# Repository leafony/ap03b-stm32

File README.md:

# Leafony AP03B STM32

AP03B STM32は、STM32duinoの既存のボード選択「Leafony AP03」を使用するマイコンリーフです。v1.1ではLQFP64の各GPIOを従来と同じLeafonyバス接点に接続します。

STM32L452RET6を搭載した、Leafony AP03B STM32リーフのハードウェア設計リポジトリです。KiCadの回路図・PCBレイアウト、単体基板のGerber・ドリルデータ、専用ライブラリ、部品表（BOM）を収録しています。

設計を開く場合は [KiCadプロジェクト](./kicad/ap03b-stm32/ap03b-stm32.kicad_pro)、部品を確認する場合は [BOM](./docs/leafony-ap03b-stm32-bom.csv) から参照してください。

## ハードウェア概要

| 項目 | 内容 |
| --- | --- |
| MCU | STMicroelectronics STM32L452RET6（U1） |
| CPU | Arm Cortex-M4、FPU搭載、最大80 MHz |
| メモリ | Flash 512 KB / SRAM 160 KB |
| MCUパッケージ | LQFP64、10 × 10 mm、0.5 mmピッチ |
| 低速外部クロック | 32.768 kHz水晶（X1） |
| 電源 | Leafonyバスの3.3 V / GND |
| バス接点 | CN1、表裏各29接点 |
| 主なバス信号 | D0〜D13、A0〜A5、SDA / SCL、SWDIO / SWCLK、RESET、AREF |
| 操作・表示 | BOOT0切り替えスイッチ、リセットスイッチ、BOOT0状態表示LED |
| 基板 | 外形最大23 × 20 mm、4層、板厚0.8 mm（PCB設計値） |
| 製造仕様 | FR-4、無電解金めっき（ENIG）。L2はGND専用層。L1・L3・L4は信号・電源を配線し、空き領域をGNDで充填。表裏のCN1バス接点のマスク開口部はGND充填の対象外 |
| 配線・ビア | 最小配線幅・間隔は0.15 mm。ビアは外径0.45 mm・穴径0.25 mmのパッド外貫通ビア |
| 設計リビジョン | v1.1、2026-11-20（単体基板・回路図のタイトル欄） |

CPU・メモリの仕様は [STMicroelectronicsの製品情報](https://www.st.com/en/microcontrollers-microprocessors/stm32l452re.html)、実装部品と接続は本リポジトリの回路図・PCB・BOMを参照しています。最大クロックはMCUの仕様値で、実際の動作クロックはファームウェアの設定によります。

CN1のVBUS端子は未接続で、AREFの接続用抵抗R5は未実装（DNP）です。各端子の接続は [Leafonyバス回路図](./kicad/ap03b-stm32/leafony_bus.kicad_sch) と [MCU回路図](./kicad/ap03b-stm32/stm32.kicad_sch) で確認できます。

### スイッチとLED

| 部品 | 型番 | 回路上の役割 |
| --- | --- | --- |
| SW1（PG） | CUS-12TB | BOOT0のHigh / Lowを切り替える |
| SW2（RST） | EVQ-P7B01P | 押すとRESETをGNDへ接続する |
| D1 | SML-A12U8TT86 | BOOT0がHighのときに点灯する。発光面は基板下辺の外側を向く |

### D1のリール供給と実装方向

ROHMの品番別仕様書（Rev.009）の図1とT86テーピング図を、次のように対応させます。供給姿勢から基板姿勢への変換は面内の回転だけです。[ROHM SML-A12U8TT86仕様書、4・5・11ページ](https://fscdn.rohm.com/en/products/databook/datasheet/opto/led/chip_mono/sml-a12u8tt86-e.pdf)

| 見る向き | カソード（K） | アノード（A） | 発光窓 |
| --- | --- | --- | --- |
| T86テープを吸着側から見て、送り穴を上に置く | 上・送り穴側 | 下 | 右 |
| 基板を部品面から見て、Leafonyバスを上に置く | 右・パッド1（GND） | 左・パッド2（R6側） | 下・基板外側 |

この二つの図の間では部品を時計回りに90°回転します。KiCadの実装座標ではD1は表面、回転角180°です。こちらの角度はフットプリントの0°を基準にしており、装着機の角度はフィーダーの取付方向と部品ライブラリの0°設定に合わせます。実装座標の原点は2ランドの中心間の中点で、F.Fab層には筐体と発光窓の輪郭を表示します。[D1の実装座標（KiCad、単位mm）](./kicad/ap03b-stm32/fabrication/ap03b-stm32-v1.1-D1-pos.csv)

U1・U2・Q1の1番ピンは、表面シルクの塗りつぶし三角が指す端子です。

詳細は [リセット・プログラム切り替え回路](./kicad/ap03b-stm32/reset_prog.kicad_sch) を参照してください。

## リポジトリ構成

| パス | 内容 |
| --- | --- |
| [kicad/ap03b-stm32/ap03b-stm32.kicad_pro](./kicad/ap03b-stm32/ap03b-stm32.kicad_pro) | 単体基板のKiCadプロジェクト |
| [kicad/ap03b-stm32/ap03b-stm32.kicad_sch](./kicad/ap03b-stm32/ap03b-stm32.kicad_sch) | トップレベル回路図。以下の3シートをまとめる |
| [kicad/ap03b-stm32/stm32.kicad_sch](./kicad/ap03b-stm32/stm32.kicad_sch) | MCU、電源、クロック周辺回路 |
| [kicad/ap03b-stm32/leafony_bus.kicad_sch](./kicad/ap03b-stm32/leafony_bus.kicad_sch) | Leafonyバス接点と信号接続 |
| [kicad/ap03b-stm32/reset_prog.kicad_sch](./kicad/ap03b-stm32/reset_prog.kicad_sch) | リセット、BOOT0切り替え、LED、信号切り替え回路 |
| [kicad/ap03b-stm32/ap03b-stm32.kicad_pcb](./kicad/ap03b-stm32/ap03b-stm32.kicad_pcb) | 単体基板のPCBレイアウト |
| [単体基板のGerber・ドリル（v1.1）](./kicad/ap03b-stm32/fabrication/ap03b-stm32-v1.1.zip) | 4層のGerber、積層情報、めっき穴と非めっき穴のドリル |
| [kicad/ap03b-stm32/panelized/](./kicad/ap03b-stm32/panelized/) | 旧版（UFBGA64・6層）の面付け基板 |
| [kicad/ap03b-stm32/panelized/Gerber/](./kicad/ap03b-stm32/panelized/Gerber/) | 旧版面付け基板のGerber・ドリルデータ |
| [kicad/ap03b-stm32/lib/](./kicad/ap03b-stm32/lib/) | Leafony専用シンボル、フットプリント、3Dモデル配置先 |
| [docs/leafony-ap03b-stm32-bom.csv](./docs/leafony-ap03b-stm32-bom.csv) | 部品表（CSV） |
| [examples/](./examples/) | サンプルコード用ディレクトリ。現時点ではコード未収録 |

KiCadプロジェクト名は `ap03b-stm32` で、設計ファイルは `kicad/ap03b-stm32/` にまとめています。

## KiCadで開く

回路図とPCBは **KiCad 10.0** で保存されています。KiCad 10.0形式を読み込める環境と、KiCad標準のシンボル・フットプリントライブラリを用意してください。

1. リポジトリを取得します。

   ```sh
   git clone https://github.com/leafony/ap03b-stm32.git
   cd ap03b-stm32
   ```

2. KiCadで `kicad/ap03b-stm32/ap03b-stm32.kicad_pro` を開きます。
3. プロジェクト内の `.kicad_sch` を開くと回路図、`.kicad_pcb` を開くと基板レイアウトを確認できます。
4. 回路図のトップシートから「STM32 MCU」「Leafony Bus」「Reset Prog」の各階層シートへ移動します。

専用ライブラリは [sym-lib-table](./kicad/ap03b-stm32/sym-lib-table) と [fp-lib-table](./kicad/ap03b-stm32/fp-lib-table) に登録済みです。どちらも `${KIPRJMOD}/lib/` を参照するため、`kicad/ap03b-stm32/` 以下のディレクトリ構成を保って開いてください。

### 面付け基板について

`kicad/ap03b-stm32/panelized/` に面付け基板のプロジェクトとPCB、同ディレクトリの `Gerber/` にGerber・ドリルデータを収録しています。

このディレクトリはUFBGA64・6層の旧版専用です。LQFP64・4層のv1.1の製造には、[単体基板のGerber・ドリル](./kicad/ap03b-stm32/fabrication/ap03b-stm32-v1.1.zip)を使用します。Leafonyバスの表裏各29接点は共通のソルダーマスク開口を使います。

## 部品表（BOM）

標準実装を100枚製造する場合の数量、単価、参照先は[部品費の内訳](./docs/parts-cost-100.md)にまとめています。

[BOMのCSV](./docs/leafony-ap03b-stm32-bom.csv) には、部品番号（Reference）、値・型番（Value）、データシート、フットプリント、数量（Qty）、実装対象外の指定（DNP）、メーカー品番（MPN）、メーカー名（MANUFACTURER）を記載しています。

- `R5`、`R7`、`R12`、`R14` は表面のオプション抵抗で、標準構成では未実装です。すべての部品のランドを表面に配置し、裏面はバス接点・配線・シルクに使用します。
- `CN1` はBOMに含まれていません。バス接点の形状・接続は回路図とPCBを参照してください。
- 部品を変更した場合は、回路図と合わせてBOMも更新してください。

## ファームウェア・関連資料

このリポジトリには、ファームウェアのビルド設定や書き込みスクリプト、実行可能なサンプルコードは含まれていません。STM32 MCUリーフの開発環境については、Leafony公式資料を参照してください。

- [STM32 MCU スタートガイド](https://docs.leafony.com/getting-started/stm32/)
- [STM32 MCU向けArduino IDEの設定](https://docs.leafony.com/environment/stm32/arduino_ide/)
- [AP03 STM32 MCU 技術資料](https://docs.leafony.com/leaf/processor/ap03/)

PlatformIOでは既存の `leafony_ap03` を選択します。AP03のデジタル・アナログ端子、I²C、SPI、UART、SWDのGPIO割り当てを維持しています。

## ライブラリとロゴの出典

`Leafony:STM32L452RET6` はKiCadライブラリ作成者による `MCU_ST_STM32L4` のシンボルを基に、AP03B用にLQFP64の端子番号と部品情報を設定しています。このシンボルにはKiCad例外付きCC BY-SA 4.0が適用されます。U1の3DモデルはKiCad標準ライブラリのLQFP64を参照します。[KiCadライブラリのライセンス](./kicad/ap03b-stm32/lib/KiCad-LICENSE.md)

裏面シルクのロゴは、Leafony公式ドキュメントのヘッダー画像を基に単色化したものです。「Leafony」はトリリオンノード研究会の登録商標です。[ロゴの出典](https://docs.leafony.com/)・[Leafonyのライセンス・商標表記](https://docs.leafony.com/license/)

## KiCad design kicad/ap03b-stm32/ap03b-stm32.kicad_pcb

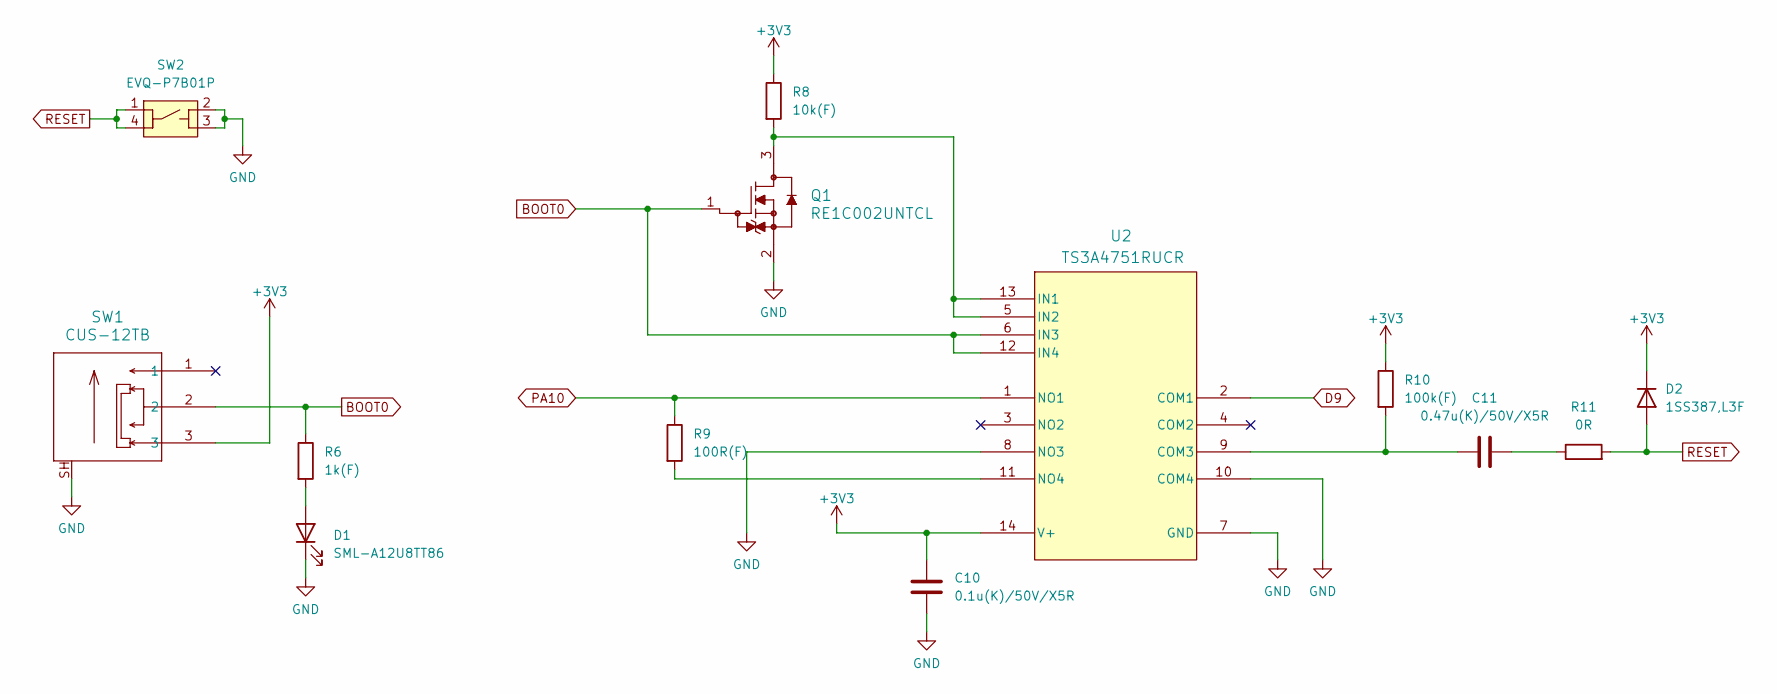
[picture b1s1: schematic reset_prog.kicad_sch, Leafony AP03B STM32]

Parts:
C10: 0.1u(K)/50V/X5R; C_0402_1005Metric; MPN CC0402KRX5R9BB104
C11: 0.47u(K)/50V/X5R; C_0402_1005Metric; MPN CC0402KRX5R9BB474
D1: SML-A12U8TT86; LED_SML-A12_ROM; MPN SML-A12U8TT86
D2: 1SS387,L3F; D_SOD-523; MPN 1SS387,L3F
Q1: RE1C002UNTCL; DIO_RB558WMF_ROM; MPN RE1C002UNTCL
R6: 1k(F); R_0402_1005Metric; MPN RC0402FR-071KL
R8: 10k(F); R_0402_1005Metric; MPN RC0402FR-0710KL
R9: 100R(F); R_0402_1005Metric; MPN RC0402FR-07100RL
R10: 100k(F); R_0402_1005Metric; MPN RC0402FR-07100KL
R11: 0R; R_0402_1005Metric; MPN RC0402JR-070RL
SW1: CUS-12TB; CUS-12TB_NDC; MPN CUS-12TB
SW2: EVQ-P7B01P; MPN EVQ-P7B01P
U2: TS3A4751RUCR; RUC14; MPN TS3A4751RUCR

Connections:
+3V3: C10.1, D2.1 (K), R8.1, R10.1, SW1.3, U2.14 (V+); also elsewhere on the board
BOOT0: Q1.1, R6.1, SW1.2, U2.6 (IN3), U2.12 (IN4); also elsewhere on the board
D9: U2.2 (COM1); also elsewhere on the board
GND: C10.2, D1.1 (K), Q1.2, SW1.SH, SW2.2, SW2.3, U2.7 (GND), U2.8 (NO3), U2.10 (COM4); also elsewhere on the board
unnamed: C11.2, R11.1
unnamed: D1.2 (A), R6.2
unnamed: C11.1, R10.2, U2.9 (COM3)
unnamed: Q1.3, R8.2, U2.5 (IN2), U2.13 (IN1)
unnamed: R9.2, U2.11 (NO4)
PA10: R9.1, U2.1 (NO1); also elsewhere on the board
RESET: D2.2 (A), R11.2, SW2.1, SW2.4; also elsewhere on the board

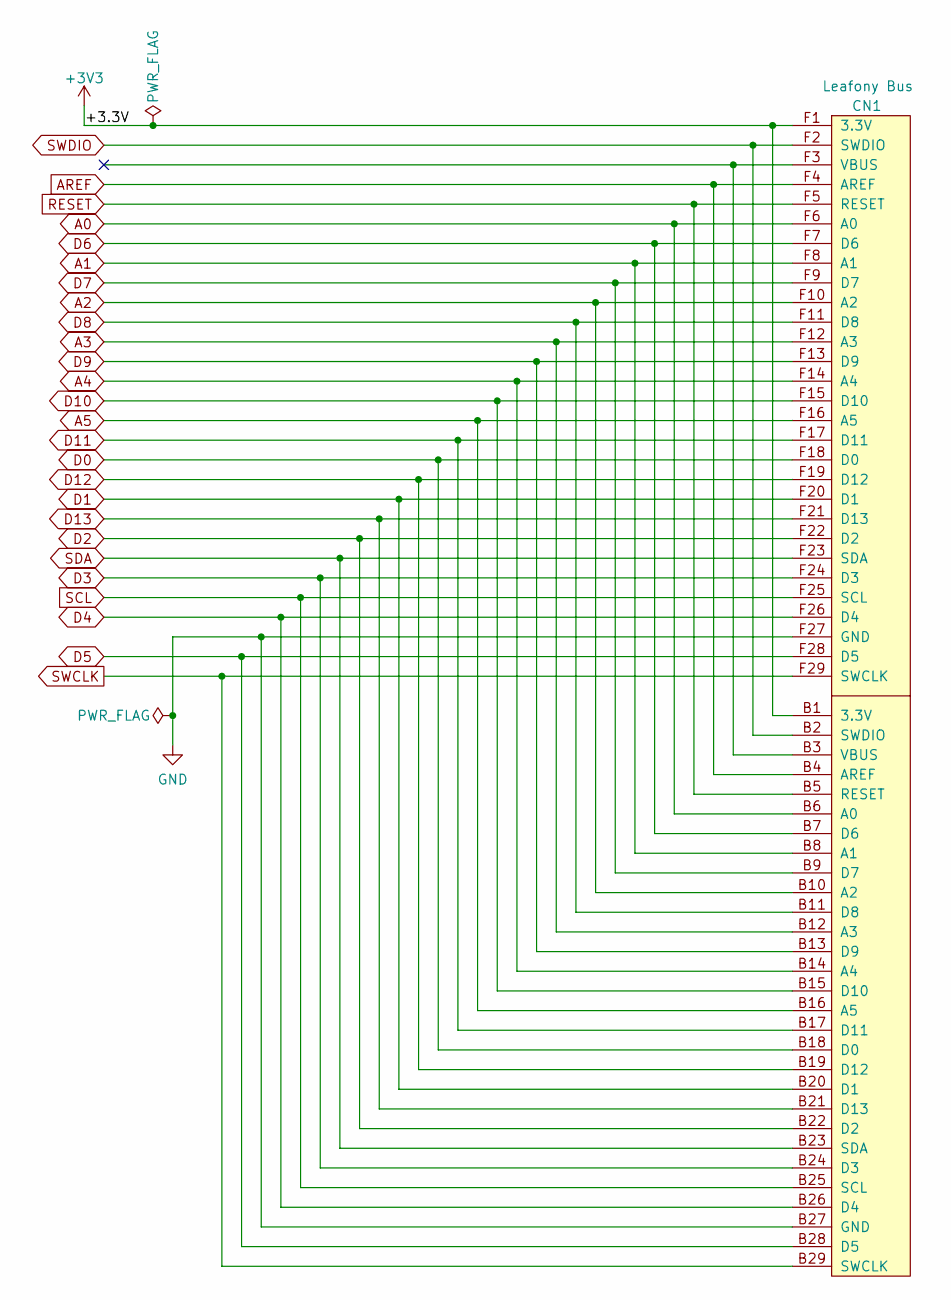
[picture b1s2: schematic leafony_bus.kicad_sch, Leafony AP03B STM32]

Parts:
CN1: Leafony Bus; CN_F29_B29

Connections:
+3V3: CN1.B1 (3.3V), CN1.F1 (3.3V); also elsewhere on the board
A0: CN1.B6 (A0), CN1.F6 (A0); also elsewhere on the board
A1: CN1.B8 (A1), CN1.F8 (A1); also elsewhere on the board
A2: CN1.B10 (A2), CN1.F10 (A2); also elsewhere on the board
A3: CN1.B12 (A3), CN1.F12 (A3); also elsewhere on the board
A4: CN1.B14 (A4), CN1.F14 (A4); also elsewhere on the board
A5: CN1.B16 (A5), CN1.F16 (A5); also elsewhere on the board
AREF: CN1.B4 (AREF), CN1.F4 (AREF); also elsewhere on the board
D0: CN1.B18 (D0), CN1.F18 (D0); also elsewhere on the board
D1: CN1.B20 (D1), CN1.F20 (D1); also elsewhere on the board
D2: CN1.B22 (D2), CN1.F22 (D2); also elsewhere on the board
D3: CN1.B24 (D3), CN1.F24 (D3); also elsewhere on the board
D4: CN1.B26 (D4), CN1.F26 (D4); also elsewhere on the board
D5: CN1.B28 (D5), CN1.F28 (D5); also elsewhere on the board
D6: CN1.B7 (D6), CN1.F7 (D6); also elsewhere on the board
D7: CN1.B9 (D7), CN1.F9 (D7); also elsewhere on the board
D8: CN1.B11 (D8), CN1.F11 (D8); also elsewhere on the board
D9: CN1.B13 (D9), CN1.F13 (D9); also elsewhere on the board
D10: CN1.B15 (D10), CN1.F15 (D10); also elsewhere on the board
D11: CN1.B17 (D11), CN1.F17 (D11); also elsewhere on the board
D12: CN1.B19 (D12), CN1.F19 (D12); also elsewhere on the board
D13: CN1.B21 (D13), CN1.F21 (D13); also elsewhere on the board
GND: CN1.B27 (GND), CN1.F27 (GND); also elsewhere on the board
RESET: CN1.B5 (RESET), CN1.F5 (RESET); also elsewhere on the board
SCL: CN1.B25 (SCL), CN1.F25 (SCL); also elsewhere on the board
SDA: CN1.B23 (SDA), CN1.F23 (SDA); also elsewhere on the board
SWCLK: CN1.B29 (SWCLK), CN1.F29 (SWCLK); also elsewhere on the board
SWDIO: CN1.B2 (SWDIO), CN1.F2 (SWDIO); also elsewhere on the board

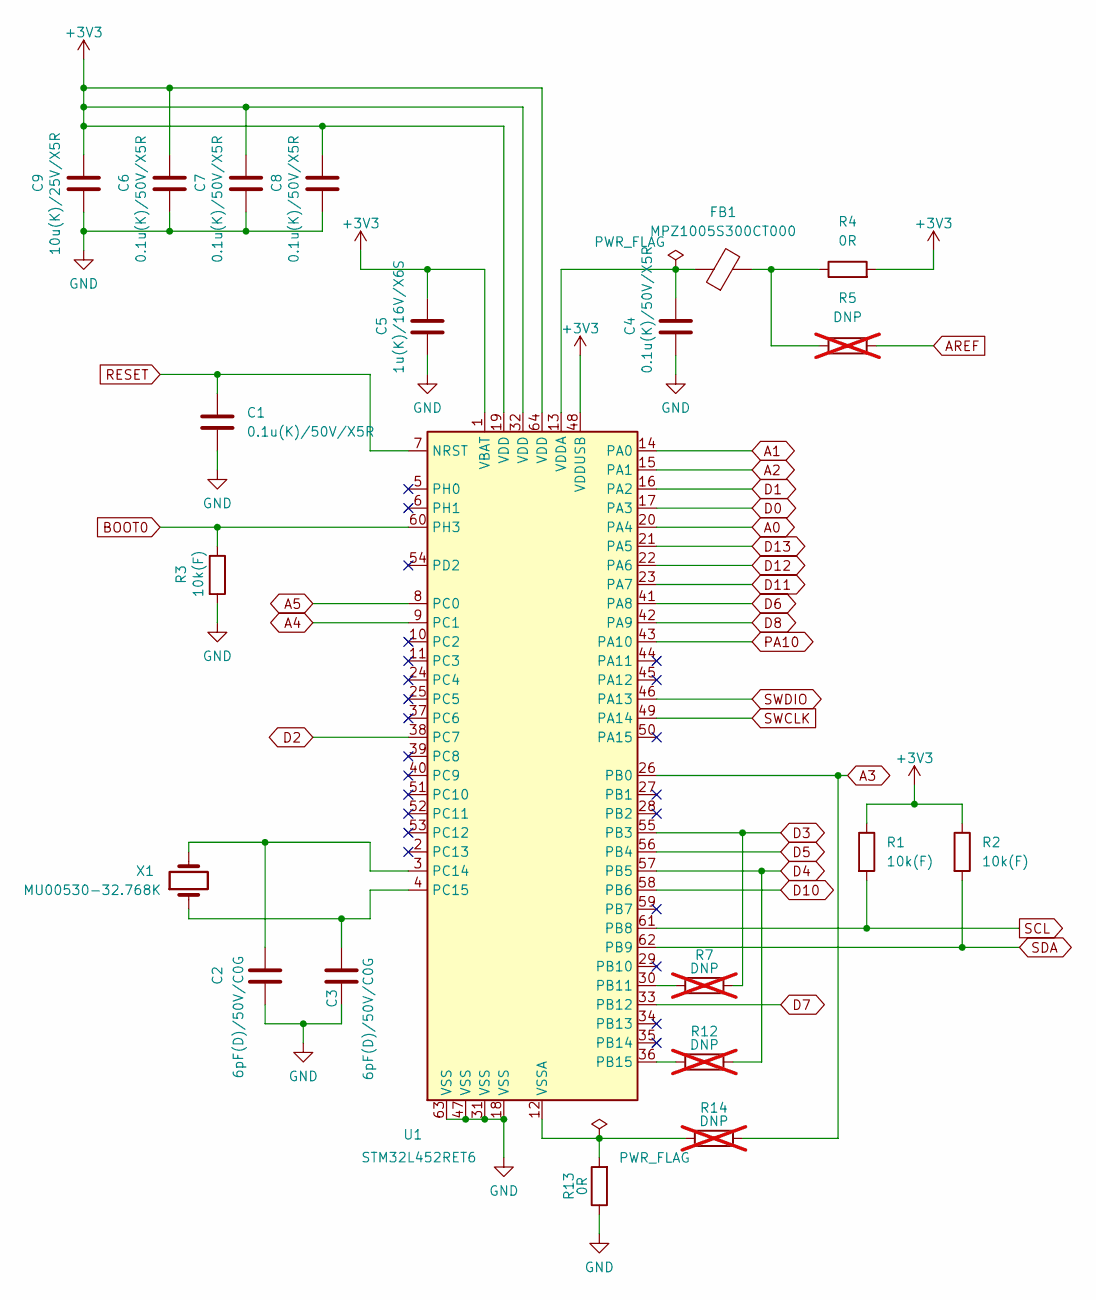
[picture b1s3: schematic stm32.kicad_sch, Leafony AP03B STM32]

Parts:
C1, C4, C6, C7, C8: 0.1u(K)/50V/X5R; C_0402_1005Metric; MPN CC0402KRX5R9BB104
C2, C3: 6pF(D)/50V/C0G; C_0402_1005Metric; MPN CC0402DRNPO9BN6R0
C5: 1u(K)/16V/X6S; C_0402_1005Metric; MPN CC0402KRX6S7BB105
C9: 10u(K)/25V/X5R; C_0603_1608Metric; MPN CC0603KRX5R8BB106
FB1: MPZ1005S300CT000; Fuse_0402_1005Metric; MPN MPZ1005S300CT000
R1, R2, R3: 10k(F); R_0402_1005Metric; MPN RC0402FR-0710KL
R4, R13: 0R; R_0402_1005Metric; MPN RC0402JR-070RL
R5, R7, R12, R14: DNP; R_0402_1005Metric; not fitted
U1: STM32L452RET6; LQFP-64_10x10mm_P0.5mm; MPN STM32L452RET6
X1: MU00530-32.768K; Crystal_SMD_2012-2Pin_2.0x1.2mm; MPN MU00530-32.768K

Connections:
+3V3: C5.1, C6.1, C7.1, C8.1, C9.1, R1.1, R2.1, R4.2, U1.1 (VBAT), U1.19 (VDD), U1.32 (VDD), U1.48 (VDDUSB), U1.64 (VDD); also elsewhere on the board
A0: U1.20 (PA4); also elsewhere on the board
A1: U1.14 (PA0); also elsewhere on the board
A2: U1.15 (PA1); also elsewhere on the board
A3: R14.2, U1.26 (PB0); also elsewhere on the board
A4: U1.9 (PC1); also elsewhere on the board
A5: U1.8 (PC0); also elsewhere on the board
AREF: R5.2; also elsewhere on the board
BOOT0: R3.1, U1.60 (PH3); also elsewhere on the board
D0: U1.17 (PA3); also elsewhere on the board
D1: U1.16 (PA2); also elsewhere on the board
D2: U1.38 (PC7); also elsewhere on the board
D3: R7.2, U1.55 (PB3); also elsewhere on the board
D4: R12.2, U1.57 (PB5); also elsewhere on the board
D5: U1.56 (PB4); also elsewhere on the board
D6: U1.41 (PA8); also elsewhere on the board
D7: U1.33 (PB12); also elsewhere on the board
D8: U1.42 (PA9); also elsewhere on the board
D10: U1.58 (PB6); also elsewhere on the board
D11: U1.23 (PA7); also elsewhere on the board
D12: U1.22 (PA6); also elsewhere on the board
D13: U1.21 (PA5); also elsewhere on the board
GND: C1.2, C2.2, C3.2, C4.2, C5.2, C6.2, C7.2, C8.2, C9.2, R3.2, R13.1, U1.18 (VSS), U1.31 (VSS), U1.47 (VSS), U1.63 (VSS); also elsewhere on the board
unnamed: FB1.2, R4.1, R5.1
unnamed: R7.1, U1.30 (PB11)
unnamed: R12.1, U1.36 (PB15)
unnamed: C2.1, U1.3 (PC14), X1.2
unnamed: C3.1, U1.4 (PC15), X1.1
unnamed: C4.1, FB1.1, U1.13 (VDDA)
unnamed: R13.2, R14.1, U1.12 (VSSA)
PA10: U1.43 (PA10); also elsewhere on the board
RESET: C1.1, U1.7 (NRST); also elsewhere on the board
SCL: R1.2, U1.61 (PB8); also elsewhere on the board
SDA: R2.2, U1.62 (PB9); also elsewhere on the board
SWCLK: U1.49 (PA14); also elsewhere on the board
SWDIO: U1.46 (PA13); also elsewhere on the board

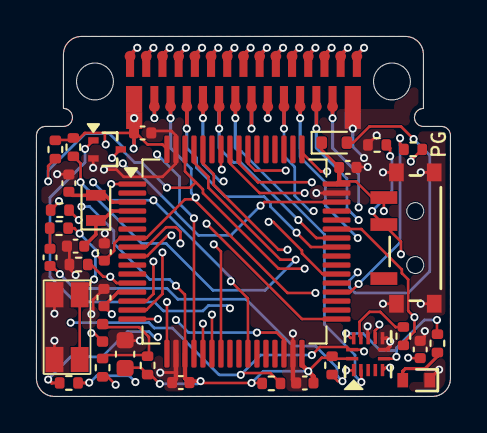
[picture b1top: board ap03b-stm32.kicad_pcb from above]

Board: 4 copper layers, 23.0 x 20.0 mm, 35 parts (0 on the bottom side), 42 nets.

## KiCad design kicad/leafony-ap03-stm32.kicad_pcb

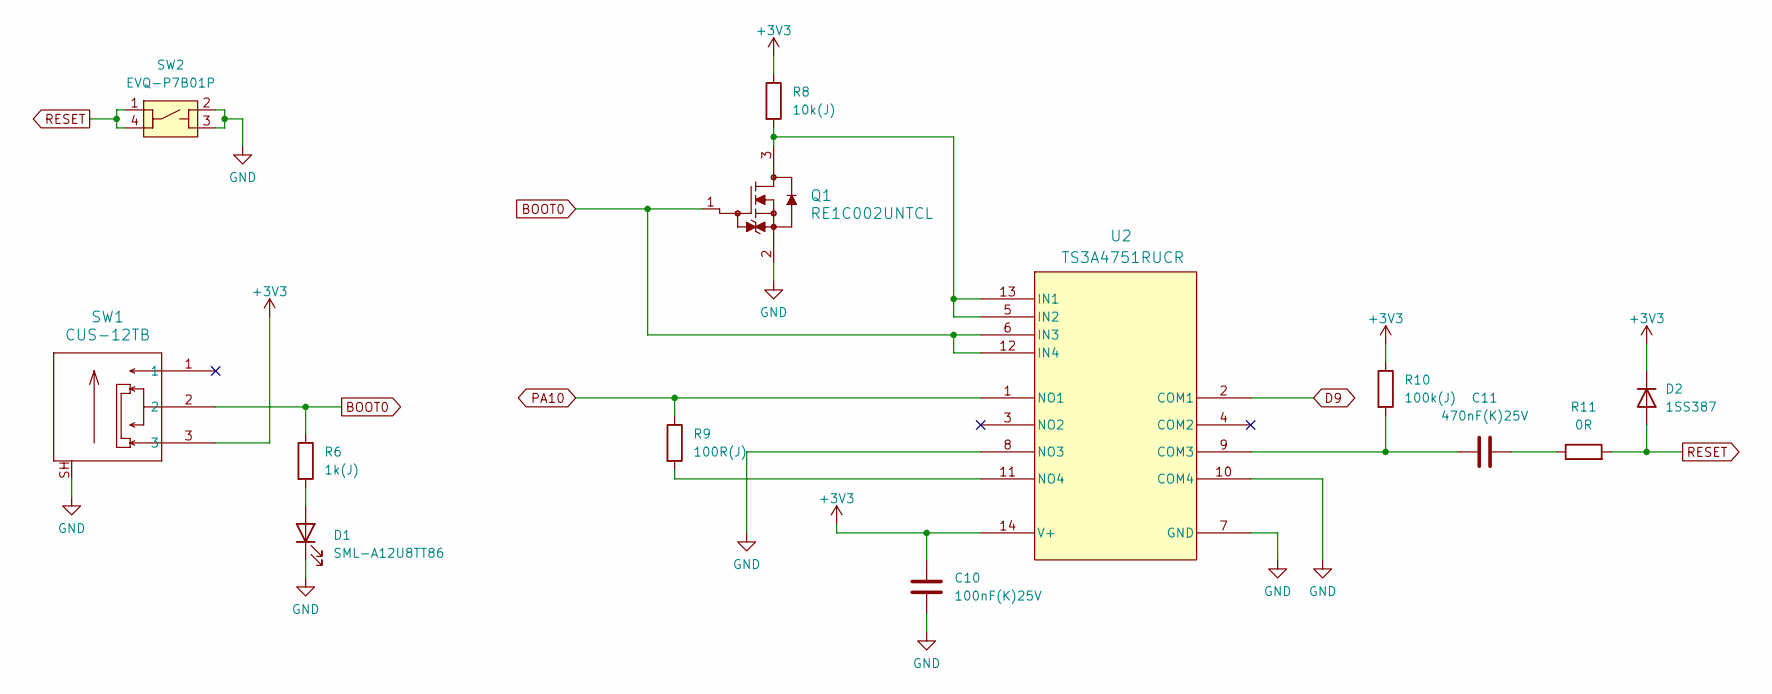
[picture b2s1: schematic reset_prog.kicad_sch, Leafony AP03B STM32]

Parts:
C10: 100nF(K)25V; C_0201_0603Metric
C11: 470nF(K)25V; C_0402_1005Metric
D1: SML-A12U8TT86; LED_SML-A12_ROM
D2: 1SS387; D_SOD-523
Q1: RE1C002UNTCL; DIO_RB558WMF_ROM
R6: 1k(J); R_0402_1005Metric
R8: 10k(J); R_0402_1005Metric
R9: 100R(J); R_0402_1005Metric
R10: 100k(J); R_0402_1005Metric
R11: 0R; R_0402_1005Metric
SW1: CUS-12TB; CUS-12TB_NDC
SW2: EVQ-P7B01P
U2: TS3A4751RUCR; RUC14

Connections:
+3V3: C10.1, D2.1 (K), R8.1, R10.1, SW1.3, U2.14 (V+); also elsewhere on the board
BOOT0: Q1.1, R6.1, SW1.2, U2.6 (IN3), U2.12 (IN4); also elsewhere on the board
D9: U2.2 (COM1); also elsewhere on the board
GND: C10.2, D1.1 (K), Q1.2, SW1.SH, SW2.2, SW2.3, U2.7 (GND), U2.8 (NO3), U2.10 (COM4); also elsewhere on the board
unnamed: C11.2, R11.1
unnamed: D1.2 (A), R6.2
unnamed: C11.1, R10.2, U2.9 (COM3)
unnamed: Q1.3, R8.2, U2.5 (IN2), U2.13 (IN1)
unnamed: R9.2, U2.11 (NO4)
PA10: R9.1, U2.1 (NO1); also elsewhere on the board
RESET: D2.2 (A), R11.2, SW2.1, SW2.4; also elsewhere on the board

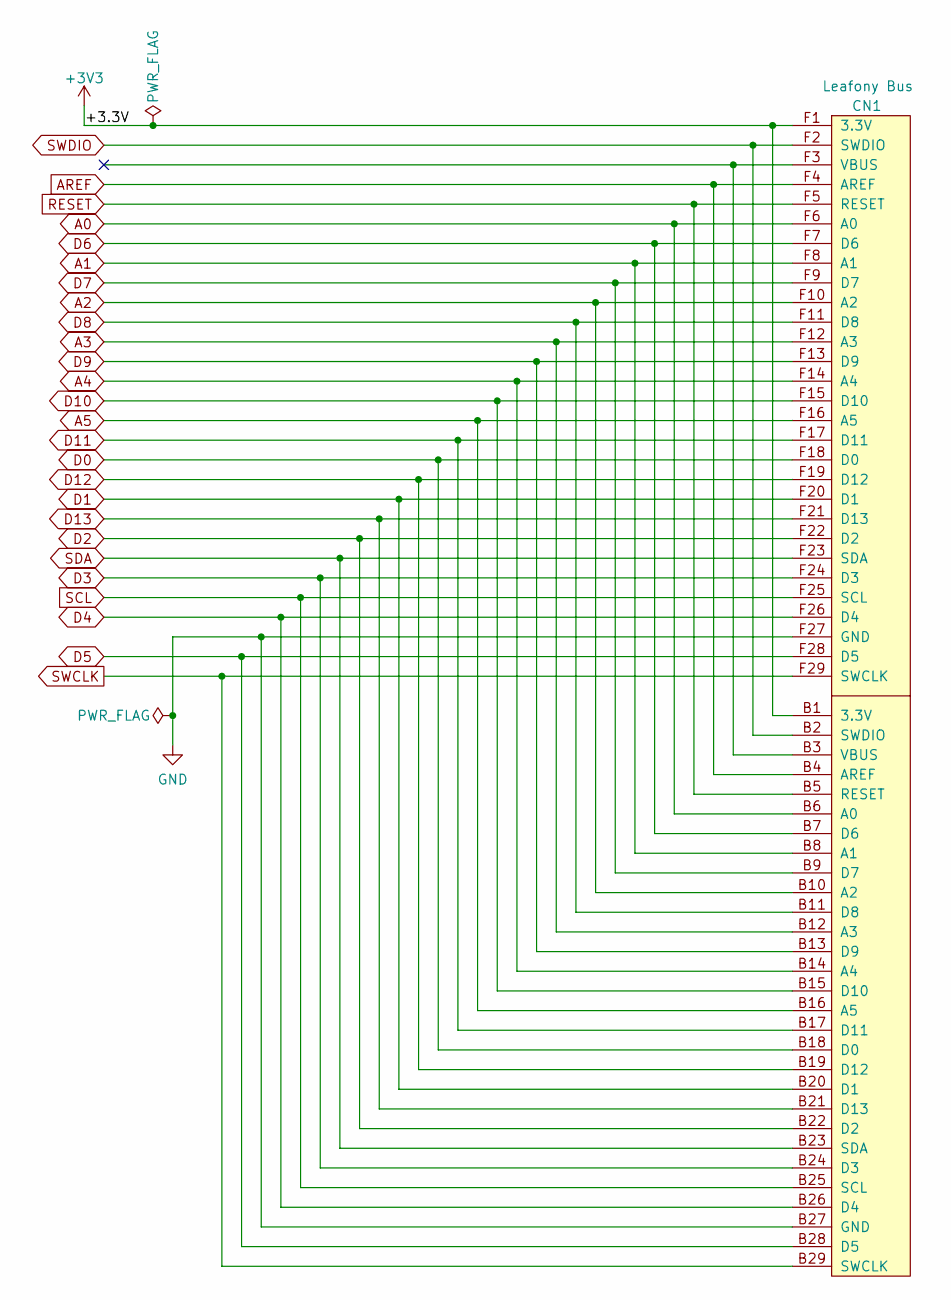
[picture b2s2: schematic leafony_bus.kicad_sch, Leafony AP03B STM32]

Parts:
CN1: Leafony Bus; CN_F29_B29

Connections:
+3V3: CN1.B1 (3.3V), CN1.F1 (3.3V); also elsewhere on the board
A0: CN1.B6 (A0), CN1.F6 (A0); also elsewhere on the board
A1: CN1.B8 (A1), CN1.F8 (A1); also elsewhere on the board
A2: CN1.B10 (A2), CN1.F10 (A2); also elsewhere on the board
A3: CN1.B12 (A3), CN1.F12 (A3); also elsewhere on the board
A4: CN1.B14 (A4), CN1.F14 (A4); also elsewhere on the board
A5: CN1.B16 (A5), CN1.F16 (A5); also elsewhere on the board
AREF: CN1.B4 (AREF), CN1.F4 (AREF); also elsewhere on the board
D0: CN1.B18 (D0), CN1.F18 (D0); also elsewhere on the board
D1: CN1.B20 (D1), CN1.F20 (D1); also elsewhere on the board
D2: CN1.B22 (D2), CN1.F22 (D2); also elsewhere on the board
D3: CN1.B24 (D3), CN1.F24 (D3); also elsewhere on the board
D4: CN1.B26 (D4), CN1.F26 (D4); also elsewhere on the board
D5: CN1.B28 (D5), CN1.F28 (D5); also elsewhere on the board
D6: CN1.B7 (D6), CN1.F7 (D6); also elsewhere on the board
D7: CN1.B9 (D7), CN1.F9 (D7); also elsewhere on the board
D8: CN1.B11 (D8), CN1.F11 (D8); also elsewhere on the board
D9: CN1.B13 (D9), CN1.F13 (D9); also elsewhere on the board
D10: CN1.B15 (D10), CN1.F15 (D10); also elsewhere on the board
D11: CN1.B17 (D11), CN1.F17 (D11); also elsewhere on the board
D12: CN1.B19 (D12), CN1.F19 (D12); also elsewhere on the board
D13: CN1.B21 (D13), CN1.F21 (D13); also elsewhere on the board
GND: CN1.B27 (GND), CN1.F27 (GND); also elsewhere on the board
RESET: CN1.B5 (RESET), CN1.F5 (RESET); also elsewhere on the board
SCL: CN1.B25 (SCL), CN1.F25 (SCL); also elsewhere on the board
SDA: CN1.B23 (SDA), CN1.F23 (SDA); also elsewhere on the board
SWCLK: CN1.B29 (SWCLK), CN1.F29 (SWCLK); also elsewhere on the board
SWDIO: CN1.B2 (SWDIO), CN1.F2 (SWDIO); also elsewhere on the board

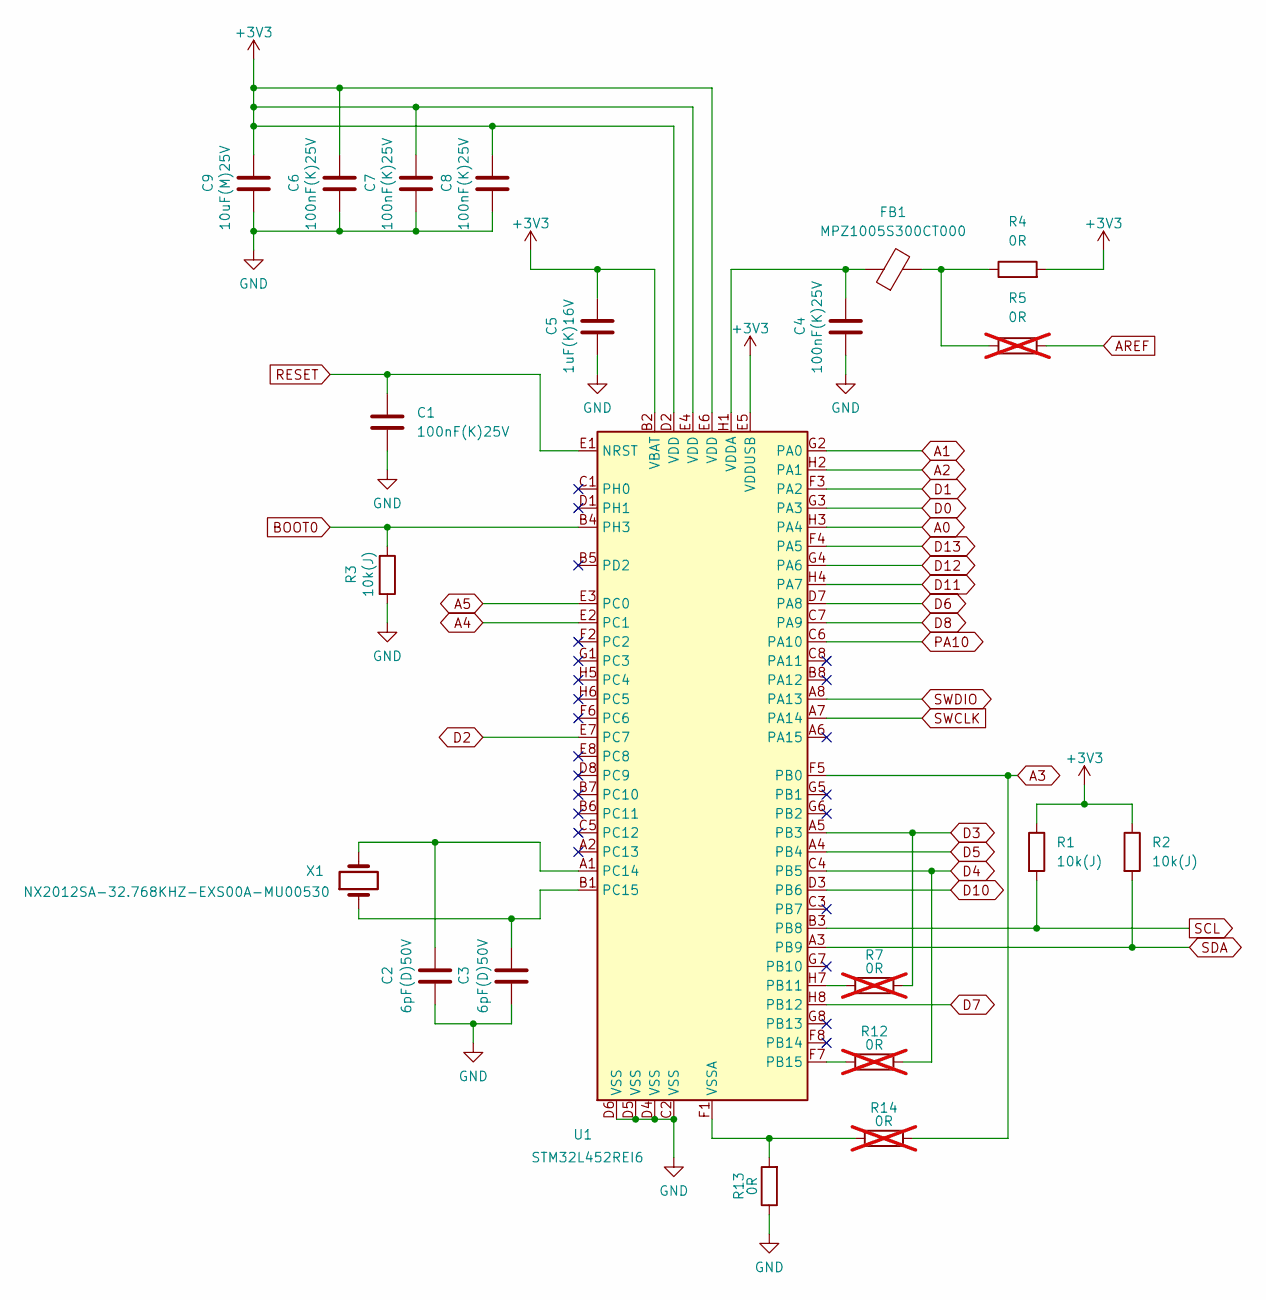
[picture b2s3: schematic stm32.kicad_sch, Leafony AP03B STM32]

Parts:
C1, C4, C6, C7, C8: 100nF(K)25V; C_0201_0603Metric
C2, C3: 6pF(D)50V; C_0402_1005Metric
C5: 1uF(K)16V; C_0402_1005Metric
C9: 10uF(M)25V; C_0603_1608Metric
FB1: MPZ1005S300CT000; Fuse_0402_1005Metric
R1, R2, R3: 10k(J); R_0402_1005Metric
R4, R13: 0R; R_0402_1005Metric
R5, R7, R12, R14: 0R; R_0402_1005Metric; not fitted
U1: STM32L452REI6; UFBGA-64_5x5mm_Layout8x8_P0.5mm
X1: NX2012SA-32.768KHZ-EXS00A-MU00530; Crystal_SMD_2012-2Pin_2.0x1.2mm

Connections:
+3V3: C5.1, C6.1, C7.1, C8.1, C9.1, R1.1, R2.1, R4.2, U1.B2 (VBAT), U1.D2 (VDD), U1.E4 (VDD), U1.E5 (VDDUSB), U1.E6 (VDD); also elsewhere on the board
A0: U1.H3 (PA4); also elsewhere on the board
A1: U1.G2 (PA0); also elsewhere on the board
A2: U1.H2 (PA1); also elsewhere on the board
A3: R14.2, U1.F5 (PB0); also elsewhere on the board
A4: U1.E2 (PC1); also elsewhere on the board
A5: U1.E3 (PC0); also elsewhere on the board
AREF: R5.2; also elsewhere on the board
BOOT0: R3.1, U1.B4 (PH3); also elsewhere on the board
D0: U1.G3 (PA3); also elsewhere on the board
D1: U1.F3 (PA2); also elsewhere on the board
D2: U1.E7 (PC7); also elsewhere on the board
D3: R7.2, U1.A5 (PB3); also elsewhere on the board
D4: R12.2, U1.C4 (PB5); also elsewhere on the board
D5: U1.A4 (PB4); also elsewhere on the board
D6: U1.D7 (PA8); also elsewhere on the board
D7: U1.H8 (PB12); also elsewhere on the board
D8: U1.C7 (PA9); also elsewhere on the board
D10: U1.D3 (PB6); also elsewhere on the board
D11: U1.H4 (PA7); also elsewhere on the board
D12: U1.G4 (PA6); also elsewhere on the board
D13: U1.F4 (PA5); also elsewhere on the board
GND: C1.2, C2.2, C3.2, C4.2, C5.2, C6.2, C7.2, C8.2, C9.2, R3.2, R13.1, U1.C2 (VSS), U1.D4 (VSS), U1.D5 (VSS), U1.D6 (VSS); also elsewhere on the board
unnamed: FB1.2, R4.1, R5.1
unnamed: R7.1, U1.H7 (PB11)
unnamed: R12.1, U1.F7 (PB15)
unnamed: C2.1, U1.A1 (PC14), X1.2
unnamed: C3.1, U1.B1 (PC15), X1.1
unnamed: C4.1, FB1.1, U1.H1 (VDDA)
unnamed: R13.2, R14.1, U1.F1 (VSSA)
PA10: U1.C6 (PA10); also elsewhere on the board
RESET: C1.1, U1.E1 (NRST); also elsewhere on the board
SCL: R1.2, U1.B3 (PB8); also elsewhere on the board
SDA: R2.2, U1.A3 (PB9); also elsewhere on the board
SWCLK: U1.A7 (PA14); also elsewhere on the board
SWDIO: U1.A8 (PA13); also elsewhere on the board

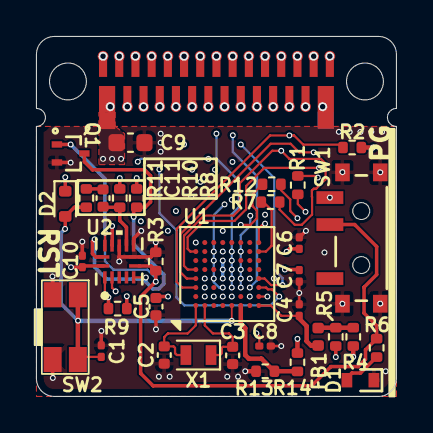
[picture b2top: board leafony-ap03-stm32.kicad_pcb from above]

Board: 6 copper layers, 20.0 x 20.0 mm, 35 parts (0 on the bottom side), 42 nets.

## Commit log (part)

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2026-04-27 回路図・レイアウトを追加
2026-04-27 BOMを追加
2026-04-27 BOMからCN1を除外
